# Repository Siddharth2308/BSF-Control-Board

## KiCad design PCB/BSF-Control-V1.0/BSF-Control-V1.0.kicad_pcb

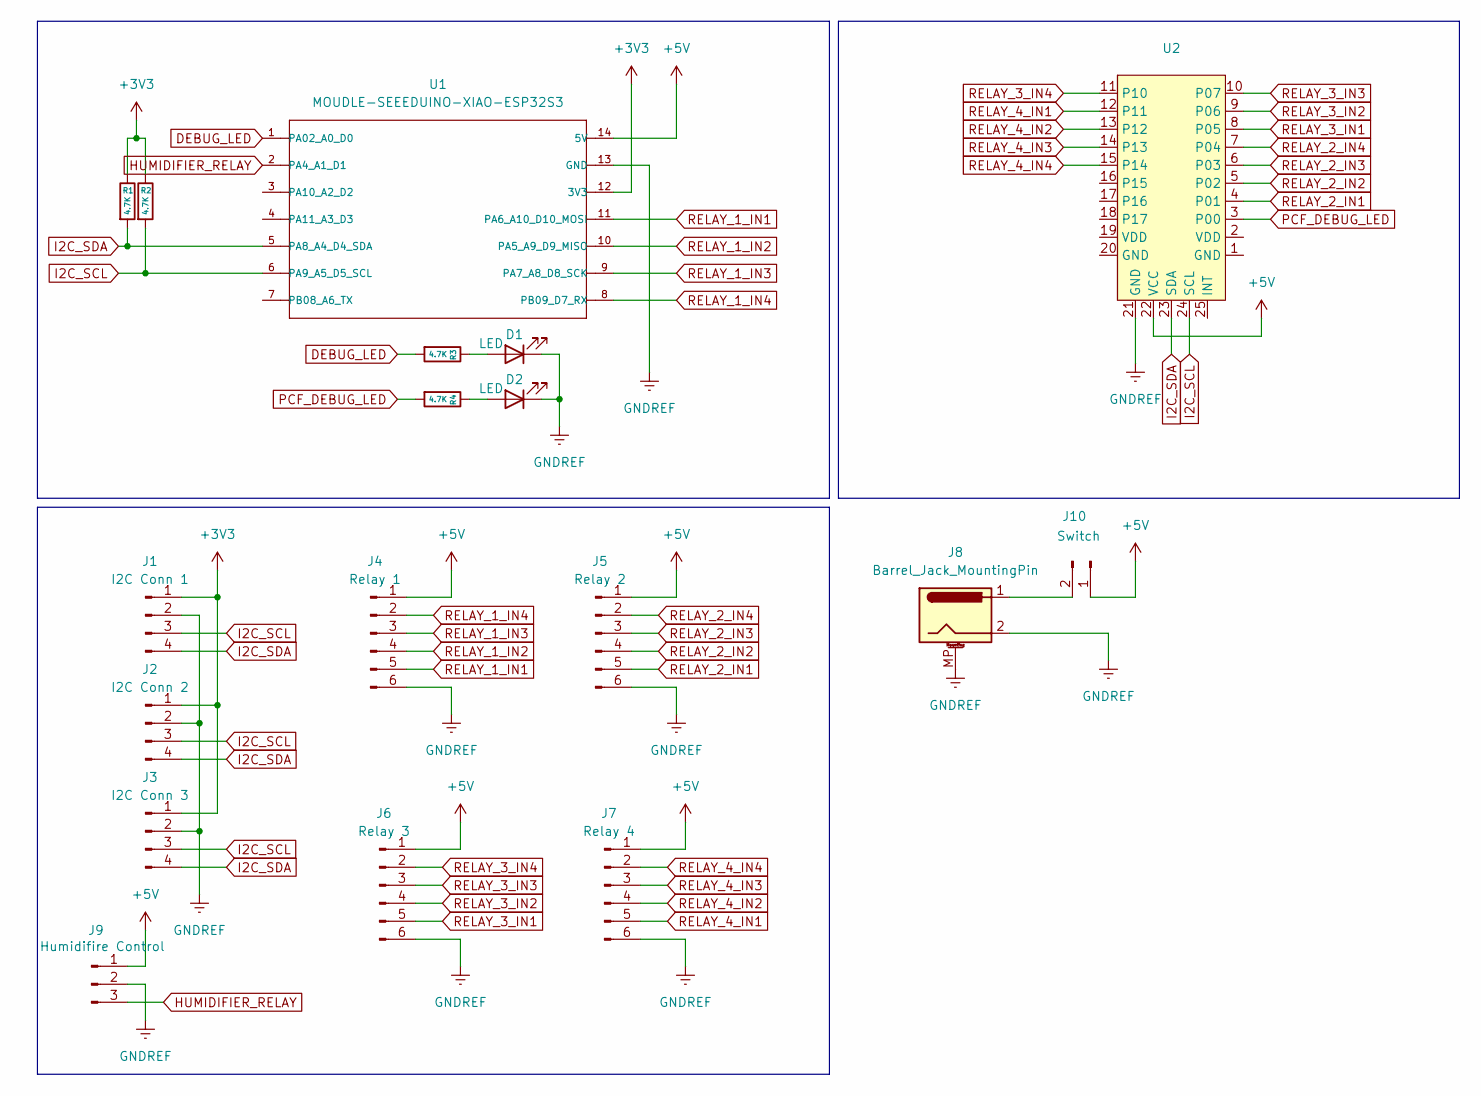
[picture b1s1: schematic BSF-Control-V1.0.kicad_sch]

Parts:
D1, D2: LED; LED_D3.0mm
J1: I2C Conn 1; Molex_SL_171971-0004_1x04_P2.54mm_Vertical
J2: I2C Conn 2; Molex_SL_171971-0004_1x04_P2.54mm_Vertical
J3: I2C Conn 3; Molex_SL_171971-0004_1x04_P2.54mm_Vertical
J4: Relay 1; Molex_SL_171971-0006_1x06_P2.54mm_Vertical
J5: Relay 2; Molex_SL_171971-0006_1x06_P2.54mm_Vertical
J6: Relay 3; Molex_SL_171971-0006_1x06_P2.54mm_Vertical
J7: Relay 4; Molex_SL_171971-0006_1x06_P2.54mm_Vertical
J8: Barrel_Jack_MountingPin; BarrelJack_Horizontal
J9: Humidifire Control; Molex_SL_171971-0003_1x03_P2.54mm_Vertical
J10: Switch; PinHeader_1x02_P2.54mm_Vertical
R1, R2, R3, R4: 4.7K; R_Axial_DIN0207_L6.3mm_D2.5mm_P7.62mm_Horizontal
U1: MOUDLE-SEEEDUINO-XIAO-ESP32S3; MOUDLE14P-SMD-2.54-21X17.8MM
U2: PCF8575_Module_ADA

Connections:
+3V3: J1.1, J2.1, J3.1, R1.1, R2.1, U1.12 (3V3)
+5V: J4.1, J5.1, J6.1, J7.1, J9.1, J10.1, U1.14 (5V), U2.22 (VCC)
DEBUG_LED: R3.2, U1.1 (PA02_A0_D0)
GNDREF: D1.1 (K), D2.1 (K), J1.2, J2.2, J3.2, J4.6, J5.6, J6.6, J7.6, J8.2, J8.MP (MountPin), J9.2, U1.13 (GND), U2.21 (GND)
HUMIDIFIER_RELAY: J9.3, U1.2 (PA4_A1_D1)
I2C_SCL: J1.3, J2.3, J3.3, R2.2, U1.6 (PA9_A5_D5_SCL), U2.24 (SCL)
I2C_SDA: J1.4, J2.4, J3.4, R1.2, U1.5 (PA8_A4_D4_SDA), U2.23 (SDA)
unnamed: D1.2 (A), R3.1
unnamed: D2.2 (A), R4.1
unnamed: J8.1, J10.2
PCF_DEBUG_LED: R4.2, U2.3 (P00)
RELAY_1_IN1: J4.5, U1.11 (PA6_A10_D10_MOSI)
RELAY_1_IN2: J4.4, U1.10 (PA5_A9_D9_MISO)
RELAY_1_IN3: J4.3, U1.9 (PA7_A8_D8_SCK)
RELAY_1_IN4: J4.2, U1.8 (PB09_D7_RX)
RELAY_2_IN1: J5.5, U2.4 (P01)
RELAY_2_IN2: J5.4, U2.5 (P02)
RELAY_2_IN3: J5.3, U2.6 (P03)
RELAY_2_IN4: J5.2, U2.7 (P04)
RELAY_3_IN1: J6.5, U2.8 (P05)
RELAY_3_IN2: J6.4, U2.9 (P06)
RELAY_3_IN3: J6.3, U2.10 (P07)
RELAY_3_IN4: J6.2, U2.11 (P10)
RELAY_4_IN1: J7.5, U2.12 (P11)
RELAY_4_IN2: J7.4, U2.13 (P12)
RELAY_4_IN3: J7.3, U2.14 (P13)
RELAY_4_IN4: J7.2, U2.15 (P14)

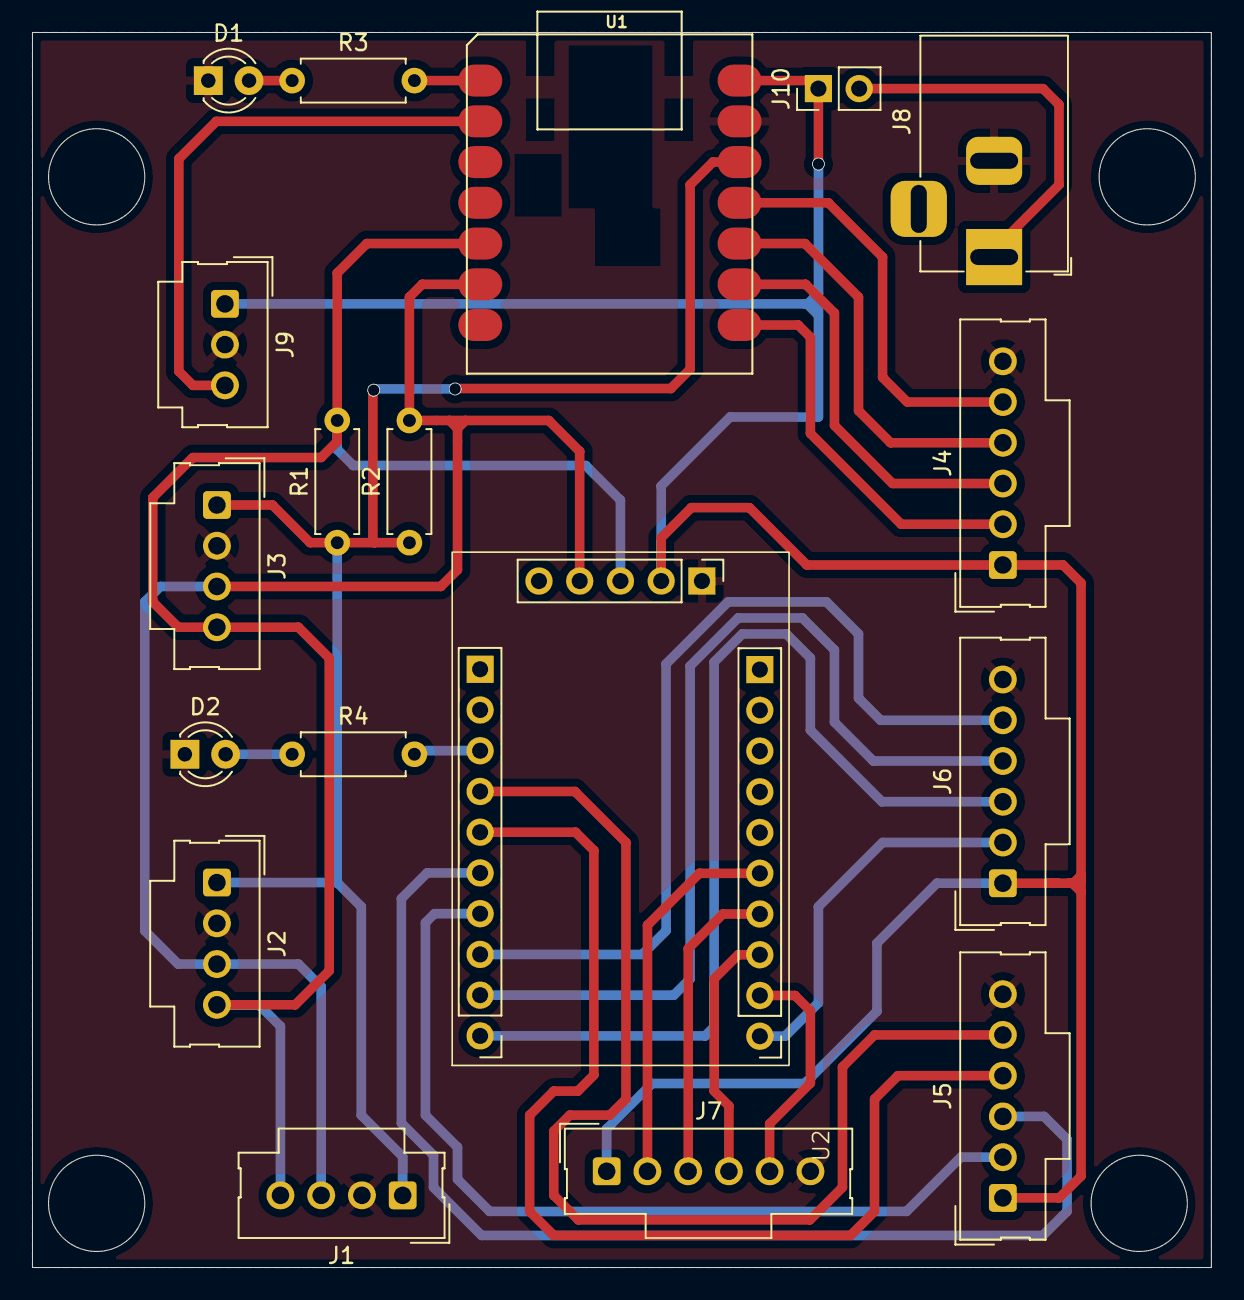
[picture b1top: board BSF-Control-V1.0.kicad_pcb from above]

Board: 2 copper layers, 73.5 x 77.0 mm, 18 parts (0 on the bottom side), 27 nets.

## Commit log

2024-08-04 PCB Done
